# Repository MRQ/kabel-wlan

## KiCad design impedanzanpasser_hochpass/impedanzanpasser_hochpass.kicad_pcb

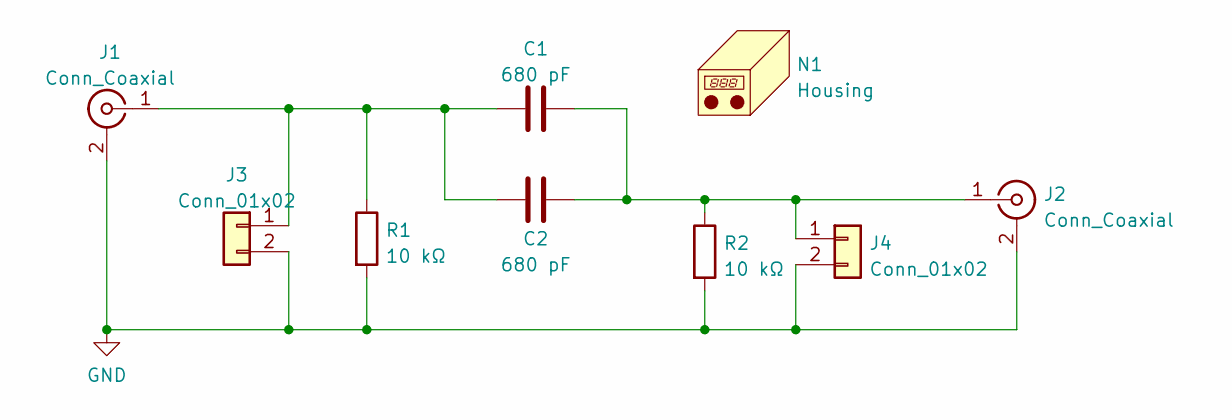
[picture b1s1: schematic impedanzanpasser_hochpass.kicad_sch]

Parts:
C1, C2: 680 pF; C_0805_2012Metric_Pad1.18x1.45mm_HandSolder
J1: Conn_Coaxial
J2: Conn_Coaxial; SMA_Molex_73251-2200_Horizontal
J3, J4: Conn_01x02; PinHeader_1x02_P2.54mm_Vertical
N1: Housing
R1, R2: 10 kΩ; R_0805_2012Metric_Pad1.20x1.40mm_HandSolder

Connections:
GND: J1.2 (Ext), J2.2 (Ext), J3.2, J4.2, R1.2, R2.2
unnamed: C1.1, C2.1, J1.1 (In), J3.1, R1.1
unnamed: C1.2, C2.2, J2.1 (In), J4.1, R2.1

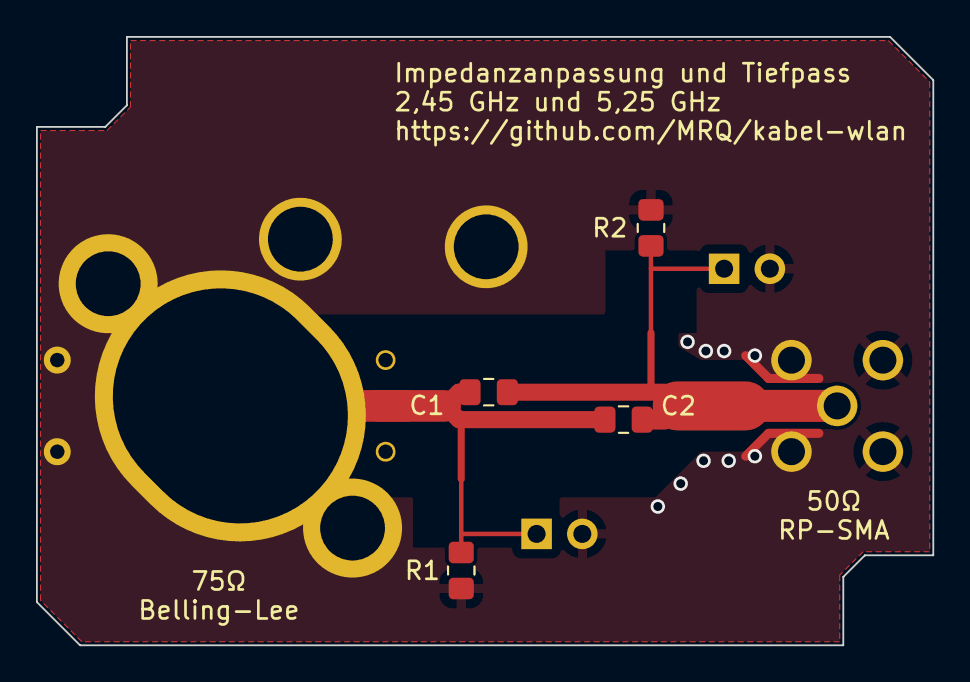
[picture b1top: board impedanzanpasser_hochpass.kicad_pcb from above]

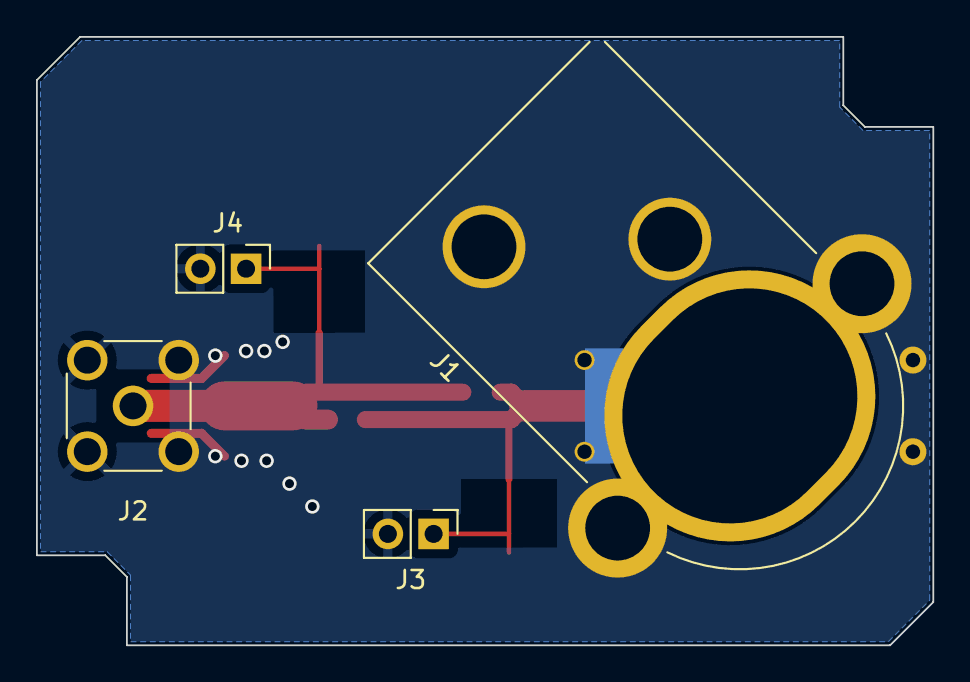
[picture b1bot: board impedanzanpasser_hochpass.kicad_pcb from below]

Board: 2 copper layers, 49.8 x 33.8 mm, 9 parts (4 on the bottom side), 3 nets.

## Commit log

2024-12-06 Impedanzanpassung, erste gefertigte Version
